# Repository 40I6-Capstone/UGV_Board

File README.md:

# UGV_Board
Board Design for UGVs

## Import Steps
- clone with git first
- open KiCAD and select open project
- select the .pro file in the cloned folder

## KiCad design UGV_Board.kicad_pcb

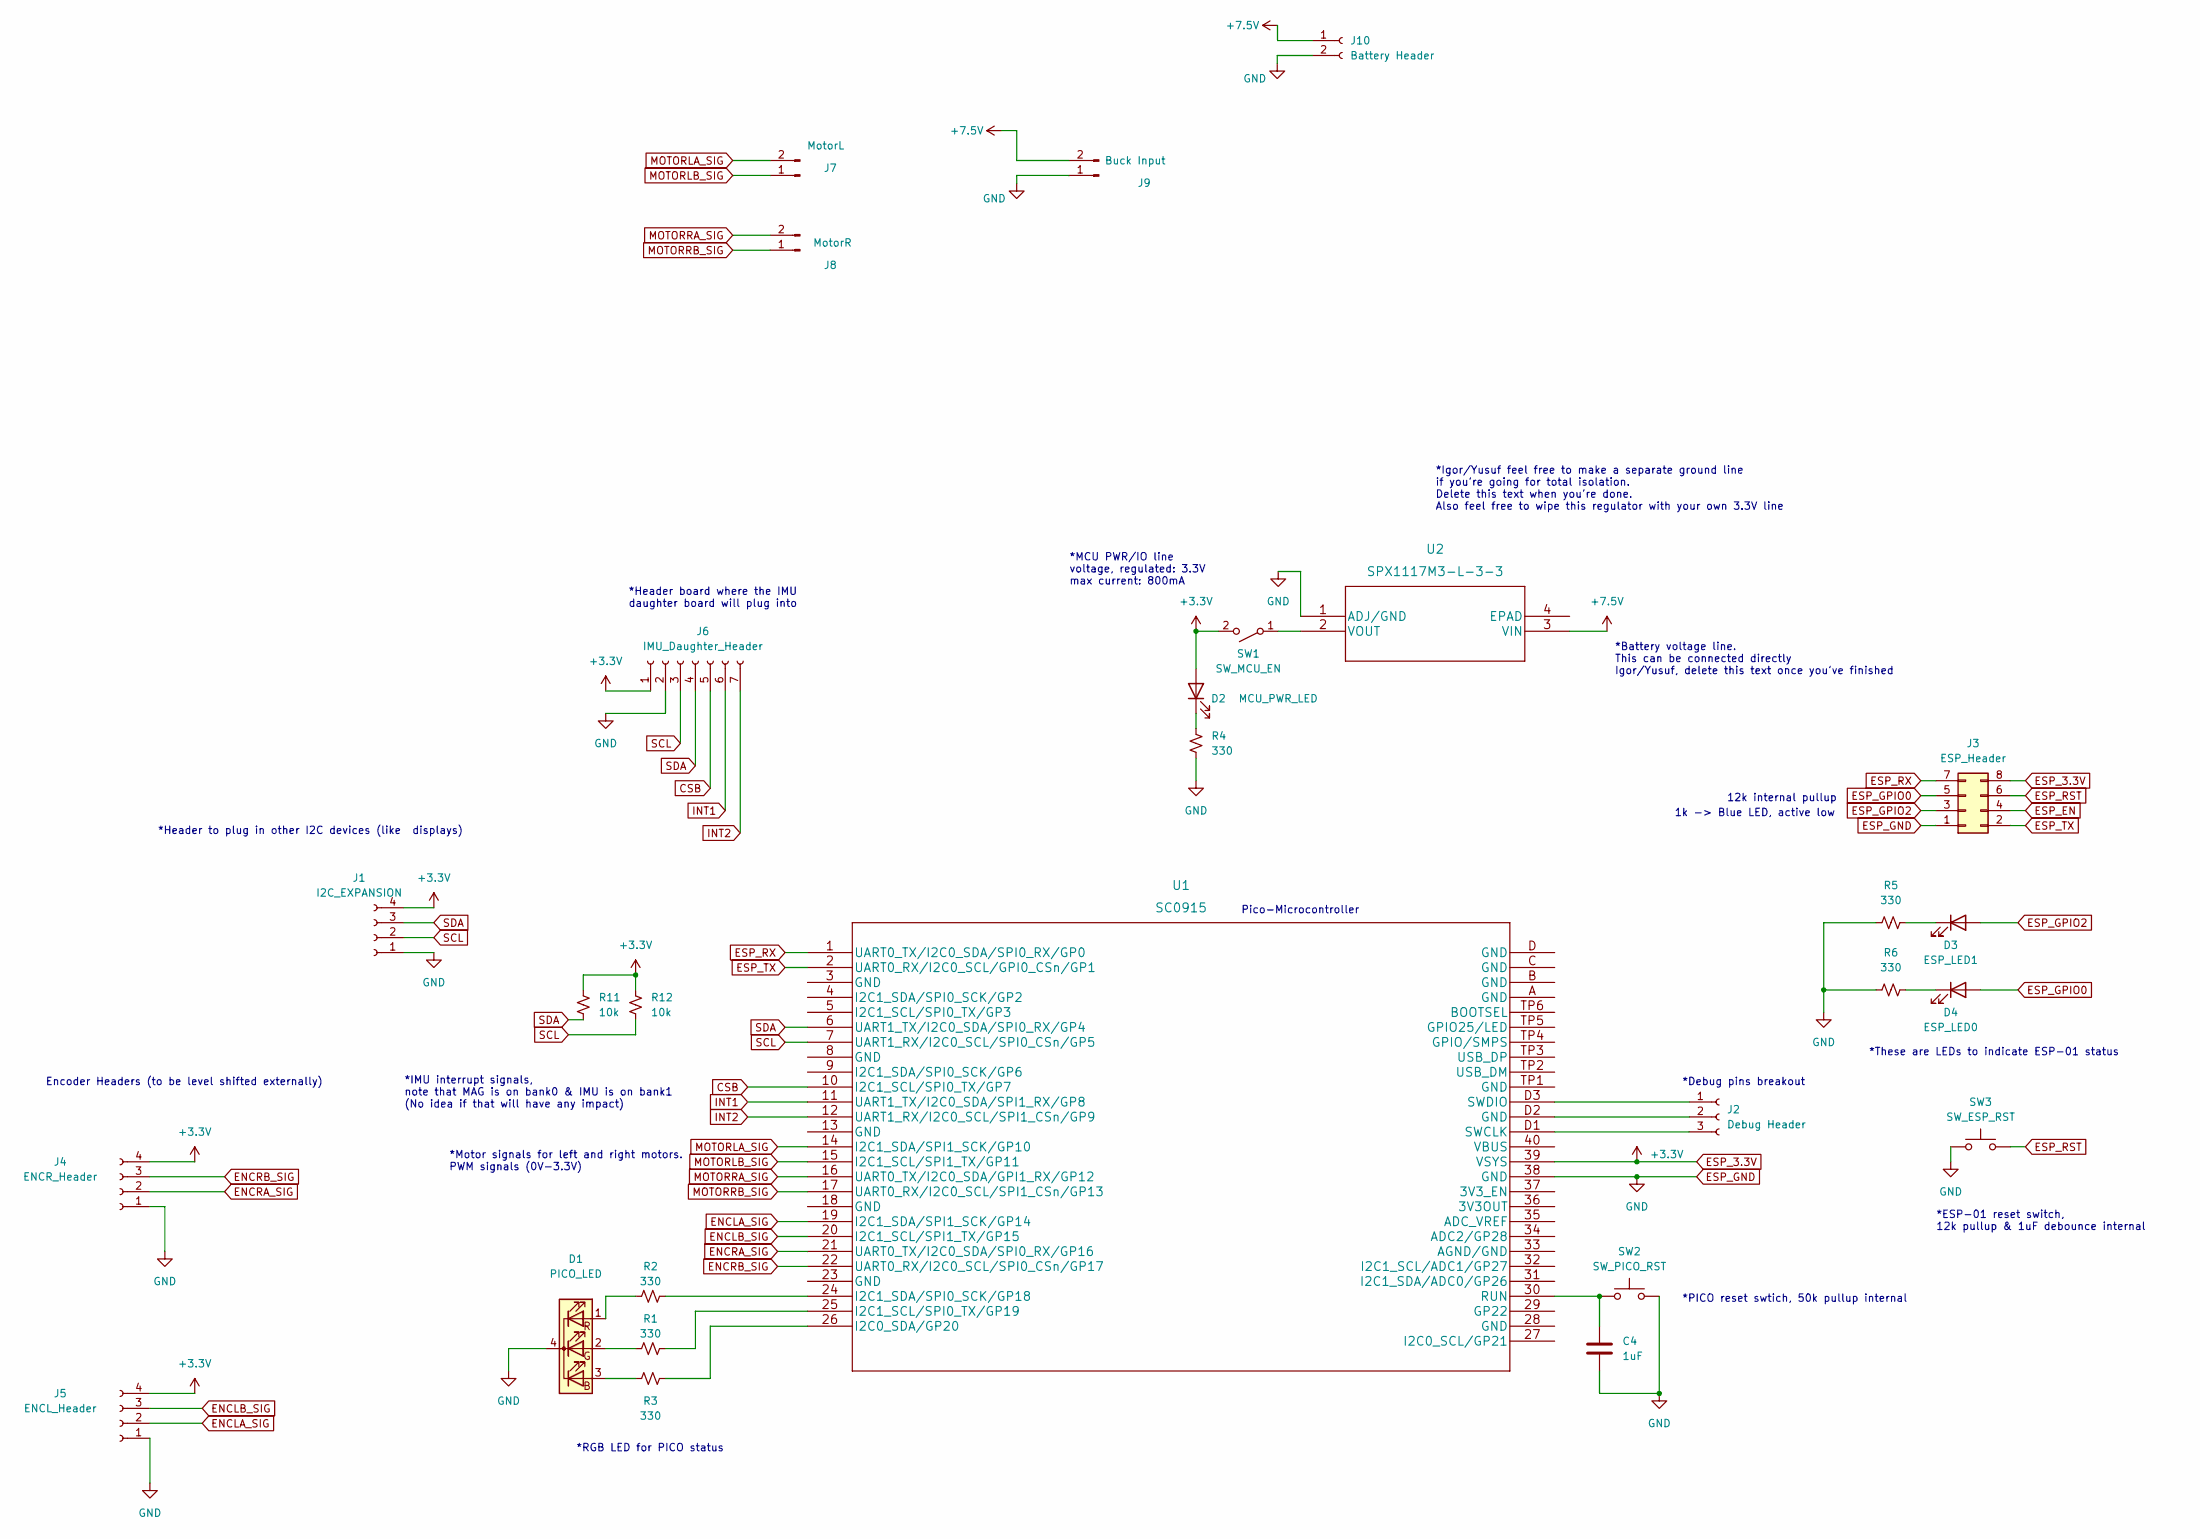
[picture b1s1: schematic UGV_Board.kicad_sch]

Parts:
C4: 1uF; C_1206_3216Metric_Pad1.33x1.80mm_HandSolder
D1: PICO_LED; LED_D5.0mm-4_RGB
D2: MCU_PWR_LED; LED_D5.0mm
D3: ESP_LED1; LED_D5.0mm
D4: ESP_LED0; LED_D5.0mm
J1: I2C_EXPANSION; PinSocket_1x04_P2.54mm_Vertical
J2: Debug Header; PinSocket_1x03_P2.54mm_Vertical
J3: ESP_Header; PinSocket_2x04_P2.54mm_Vertical
J4: ENCR_Header; PinSocket_1x04_P2.54mm_Vertical
J5: ENCL_Header; PinSocket_1x04_P2.54mm_Vertical
J6: IMU_Daughter_Header; PinHeader_1x07_P2.54mm_Vertical
J7: MotorL; PinSocket_1x02_P2.54mm_Vertical
J8: MotorR; PinSocket_1x02_P2.54mm_Vertical
J9: Buck Input; PinSocket_1x02_P2.54mm_Vertical
J10: Battery Header; PinSocket_1x02_P2.54mm_Vertical
R1, R2, R3, R4, R5, R6: 330; R_1206_3216Metric_Pad1.30x1.75mm_HandSolder
R11, R12: 10k; R_1206_3216Metric_Pad1.30x1.75mm_HandSolder
SW1: SW_MCU_EN; PinHeader_1x02_P2.54mm_Vertical
SW2: SW_PICO_RST; SW_PUSH_6mm_H4.3mm
SW3: SW_ESP_RST; SW_PUSH_6mm_H4.3mm
U1: SC0915
U2: SPX1117M3-L-3-3; SPX1117M3-L-3-3&slash_TR

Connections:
+7.5V: J9.2, J10.1, U2.3 (VIN)
CSB: J6.5, U1.10 (I2C1_SCL/SPI0_TX/GP7)
ENCLA_SIG: J5.2, U1.19 (I2C1_SDA/SPI1_SCK/GP14)
ENCLB_SIG: J5.3, U1.20 (I2C1_SCL/SPI1_TX/GP15)
ENCRA_SIG: J4.2, U1.21 (UART0_TX/I2C0_SDA/SPI0_RX/GP16)
ENCRB_SIG: J4.3, U1.22 (UART0_RX/I2C0_SCL/SPI0_CSn/GP17)
ESP_3.3V: D2.2 (A), J1.4, J3.8, J4.4, J5.4, J6.1, R11.2, R12.2, SW1.2 (B), U1.39 (VSYS)
ESP_EN: J3.4
ESP_GND: C4.2, D1.4 (K), J1.1, J3.1, J4.1, J5.1, J6.2, J9.1, J10.2, R4.1, R5.1, R6.1, SW2.2, SW3.1, U1.38 (GND), U2.1 (ADJ/GND)
ESP_GPIO0: D4.2 (A), J3.5
ESP_GPIO2: D3.2 (A), J3.3
ESP_RST: J3.6, SW3.2
ESP_RX: J3.7, U1.1 (UART0_TX/I2C0_SDA/SPI0_RX/GP0)
ESP_TX: J3.2, U1.2 (UART0_RX/I2C0_SCL/GPI0_CSn/GP1)
INT1: J6.6, U1.11 (UART1_TX/I2C0_SDA/SPI1_RX/GP8)
INT2: J6.7, U1.12 (UART1_RX/I2C0_SCL/SPI1_CSn/GP9)
MOTORLA_SIG: J7.2, U1.14 (I2C1_SDA/SPI1_SCK/GP10)
MOTORLB_SIG: J7.1, U1.15 (I2C1_SCL/SPI1_TX/GP11)
MOTORRA_SIG: J8.2, U1.16 (UART0_TX/I2C0_SDA/GPI1_RX/GP12)
MOTORRB_SIG: J8.1, U1.17 (UART0_RX/I2C0_SCL/SPI1_CSn/GP13)
unnamed: C4.1, SW2.1, U1.30 (RUN)
unnamed: D1.1 (RA), R2.1
unnamed: D1.2 (GA), R1.1
unnamed: D1.3 (BA), R3.1
unnamed: D2.1 (K), R4.2
unnamed: D3.1 (K), R5.2
unnamed: D4.1 (K), R6.2
unnamed: J2.1, U1.D3 (SWDIO)
unnamed: J2.2, U1.D2 (GND)
unnamed: J2.3, U1.D1 (SWCLK)
unnamed: R1.2, U1.25 (I2C1_SCL/SPI0_TX/GP19)
unnamed: R2.2, U1.24 (I2C1_SDA/SPI0_SCK/GP18)
unnamed: R3.2, U1.26 (I2C0_SDA/GP20)
unnamed: SW1.1 (A), U2.2 (VOUT)
SCL: J1.2, J6.3, R12.1, U1.7 (UART1_RX/I2C0_SCL/SPI0_CSn/GP5)
SDA: J1.3, J6.4, R11.1, U1.6 (UART1_TX/I2C0_SDA/SPI0_RX/GP4)

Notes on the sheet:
*ESP-01 reset switch, 12k pullup & 1uF debounce internal
Pico-Microcontroller
*PICO reset swtich, 50k pullup internal
*Battery voltage line. This can be connected directly Igor/Yusuf, delete this text once you've finished
*IMU interrupt signals, note that MAG is on bank0 & IMU is on bank1 (No idea if that will have any impact)
*Header board where the IMU daughter board will plug into
12k internal pullup
*Header to plug in other I2C devices (like displays)
*RGB LED for PICO status
*Debug pins breakout
*MCU PWR/IO line voltage, regulated: 3.3V max current: 800mA
*Motor signals for left and right motors. PWM signals (0V-3.3V)
Encoder Headers (to be level shifted externally)
1k -> Blue LED, active low
*These are LEDs to indicate ESP-01 status
*Igor/Yusuf feel free to make a separate ground line if you're going for total isolation. Delete this text when you're done. Also feel free to wipe this regulator with your own 3.3V line

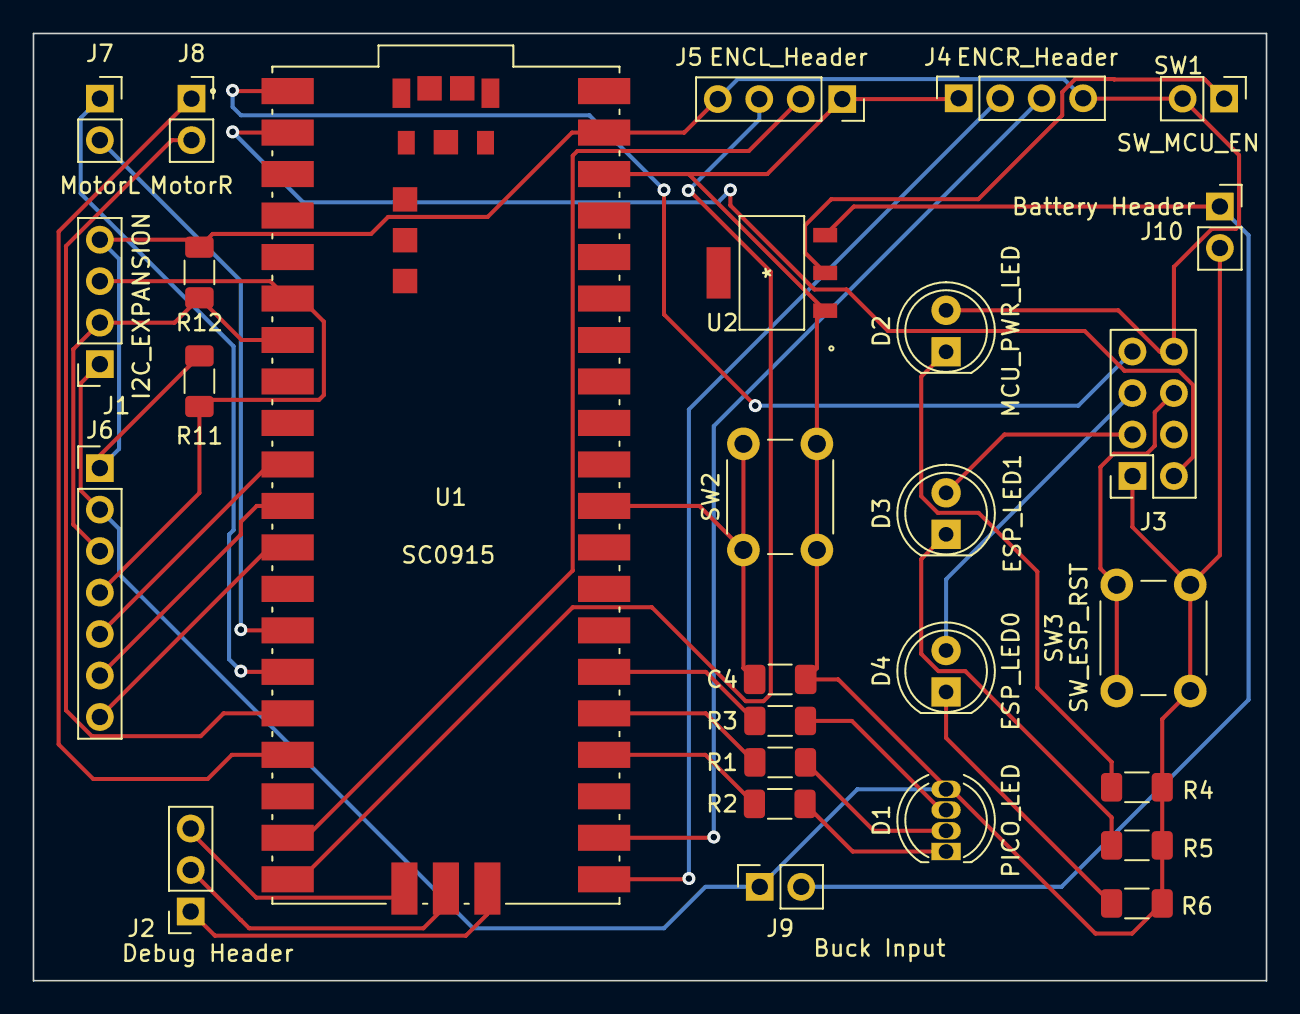
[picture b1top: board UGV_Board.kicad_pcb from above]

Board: 2 copper layers, 75.5 x 58.0 mm, 28 parts (0 on the bottom side), 35 nets.

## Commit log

2022-11-15 first revision of mcu hardware schematic
2022-11-17 mcu control circuitry
2022-12-06 Buck + H-Bridge
    Added
    -Buck Convertor
    -H-Bridge
2022-12-06 Assigned footprints
2022-12-06 floating en pin
2022-12-06 fixed i2c header footprint
2023-01-12 Jan 12
2023-01-13 plugged mcu into h-bridge
2023-01-20 Completed KiKad First Draft
2023-01-30 Pullups on comparators
2023-02-01 Rev 1 Final
2023-02-06 final changes
2023-02-17 v2 schematic
2023-02-18 KiKAD Rev 2 Feb 17
2023-04-06 final

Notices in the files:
parts and their libraries:
Copyright 2021 Accelerated Designs. All rights reserved.
